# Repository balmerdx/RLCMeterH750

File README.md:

# RLCMeterH750
Это RLC построенный на STM32H750.
Основные отличительные особенности:
* использование быстрого 16-ти битного ADC от STM32H750
* широкий диапазон тестовых частот 10 Гц - 500 КГц
* построение графиков параметров в зависимости от частоты

Про точность не буду сильно распинаться, ибо сам точно не знаю.
Но приблизительно опишу.
Сопротивления измеряются в диапазоне от единиц миллиом до сотен килоом.
Но десятые доли пикофарада без проблемм можно измерить. На частотах 100 КГц и выше.
Десятки наногенри тоже вполне можно измерять. Тоже на высоких частотах, но тут желательно теорию подучить, чтобы понимать что измеряется.
На низких частотах вполне можно измерять десятки милифарад и единицы генри.

И да, внимание!!!! Финальной PCB нет в этом проекте. На плату RLCMeterH750_v2 я вкорячил детали от схемы RLCMeterH750_v3. Собственно говоря вариант RLCMeterH750_v2 тоже полностью рабочий, но он имеет отвратительно большие ошибки на частотах ниже 300 Гц. RLCMeterH750_v3 исправляет резонансы, которые были не учтены мной.

А ещё этот RLC измеритель умеет строить графики значений в зависимости от частоты. Вот пример измерения катушки индуктивности от реле. Красная линия - вещественная часть сопротивления, зелёная - мнимая часть сопротивления. Естественно железный сердечник ведёт себя совсем не так, как хорошая катушка индуктивности.

### Тут много ссылок на посты в Livejournal про то как шла разработка.
* [Пост 157420](https://balmerdx.livejournal.com/157420.html)
* [Пост 157827](https://balmerdx.livejournal.com/157827.html)
* [Пост 158370](https://balmerdx.livejournal.com/158370.html)
* [Пост 159728](https://balmerdx.livejournal.com/159728.html)
* [Пост 160005](https://balmerdx.livejournal.com/160005.html)
* [Пост 160708](https://balmerdx.livejournal.com/160708.html)
* [Пост 160803](https://balmerdx.livejournal.com/160803.html)
* [Пост 161141](https://balmerdx.livejournal.com/161141.html)
* [Пост 161592](https://balmerdx.livejournal.com/161592.html)

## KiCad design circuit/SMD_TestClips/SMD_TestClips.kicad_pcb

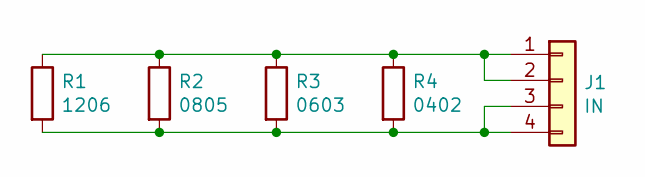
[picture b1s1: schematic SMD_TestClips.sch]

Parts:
J1: IN; PinHeader_1x04_P2.54mm_Vertical
R1: 1206; R_1206_3216Metric
R2: 0805; R_0805_2012Metric
R3: 0603; R_0603_1608Metric
R4: 0402; R_0402_1005Metric

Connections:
unnamed: J1.1, J1.2, R1.1, R2.1, R3.1, R4.1
unnamed: J1.3, J1.4, R1.2, R2.2, R3.2, R4.2

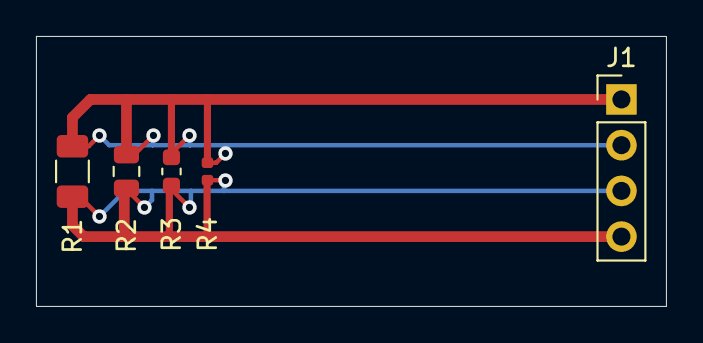
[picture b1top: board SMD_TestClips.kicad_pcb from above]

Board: 2 copper layers, 35.0 x 15.0 mm, 5 parts (0 on the bottom side), 2 nets.

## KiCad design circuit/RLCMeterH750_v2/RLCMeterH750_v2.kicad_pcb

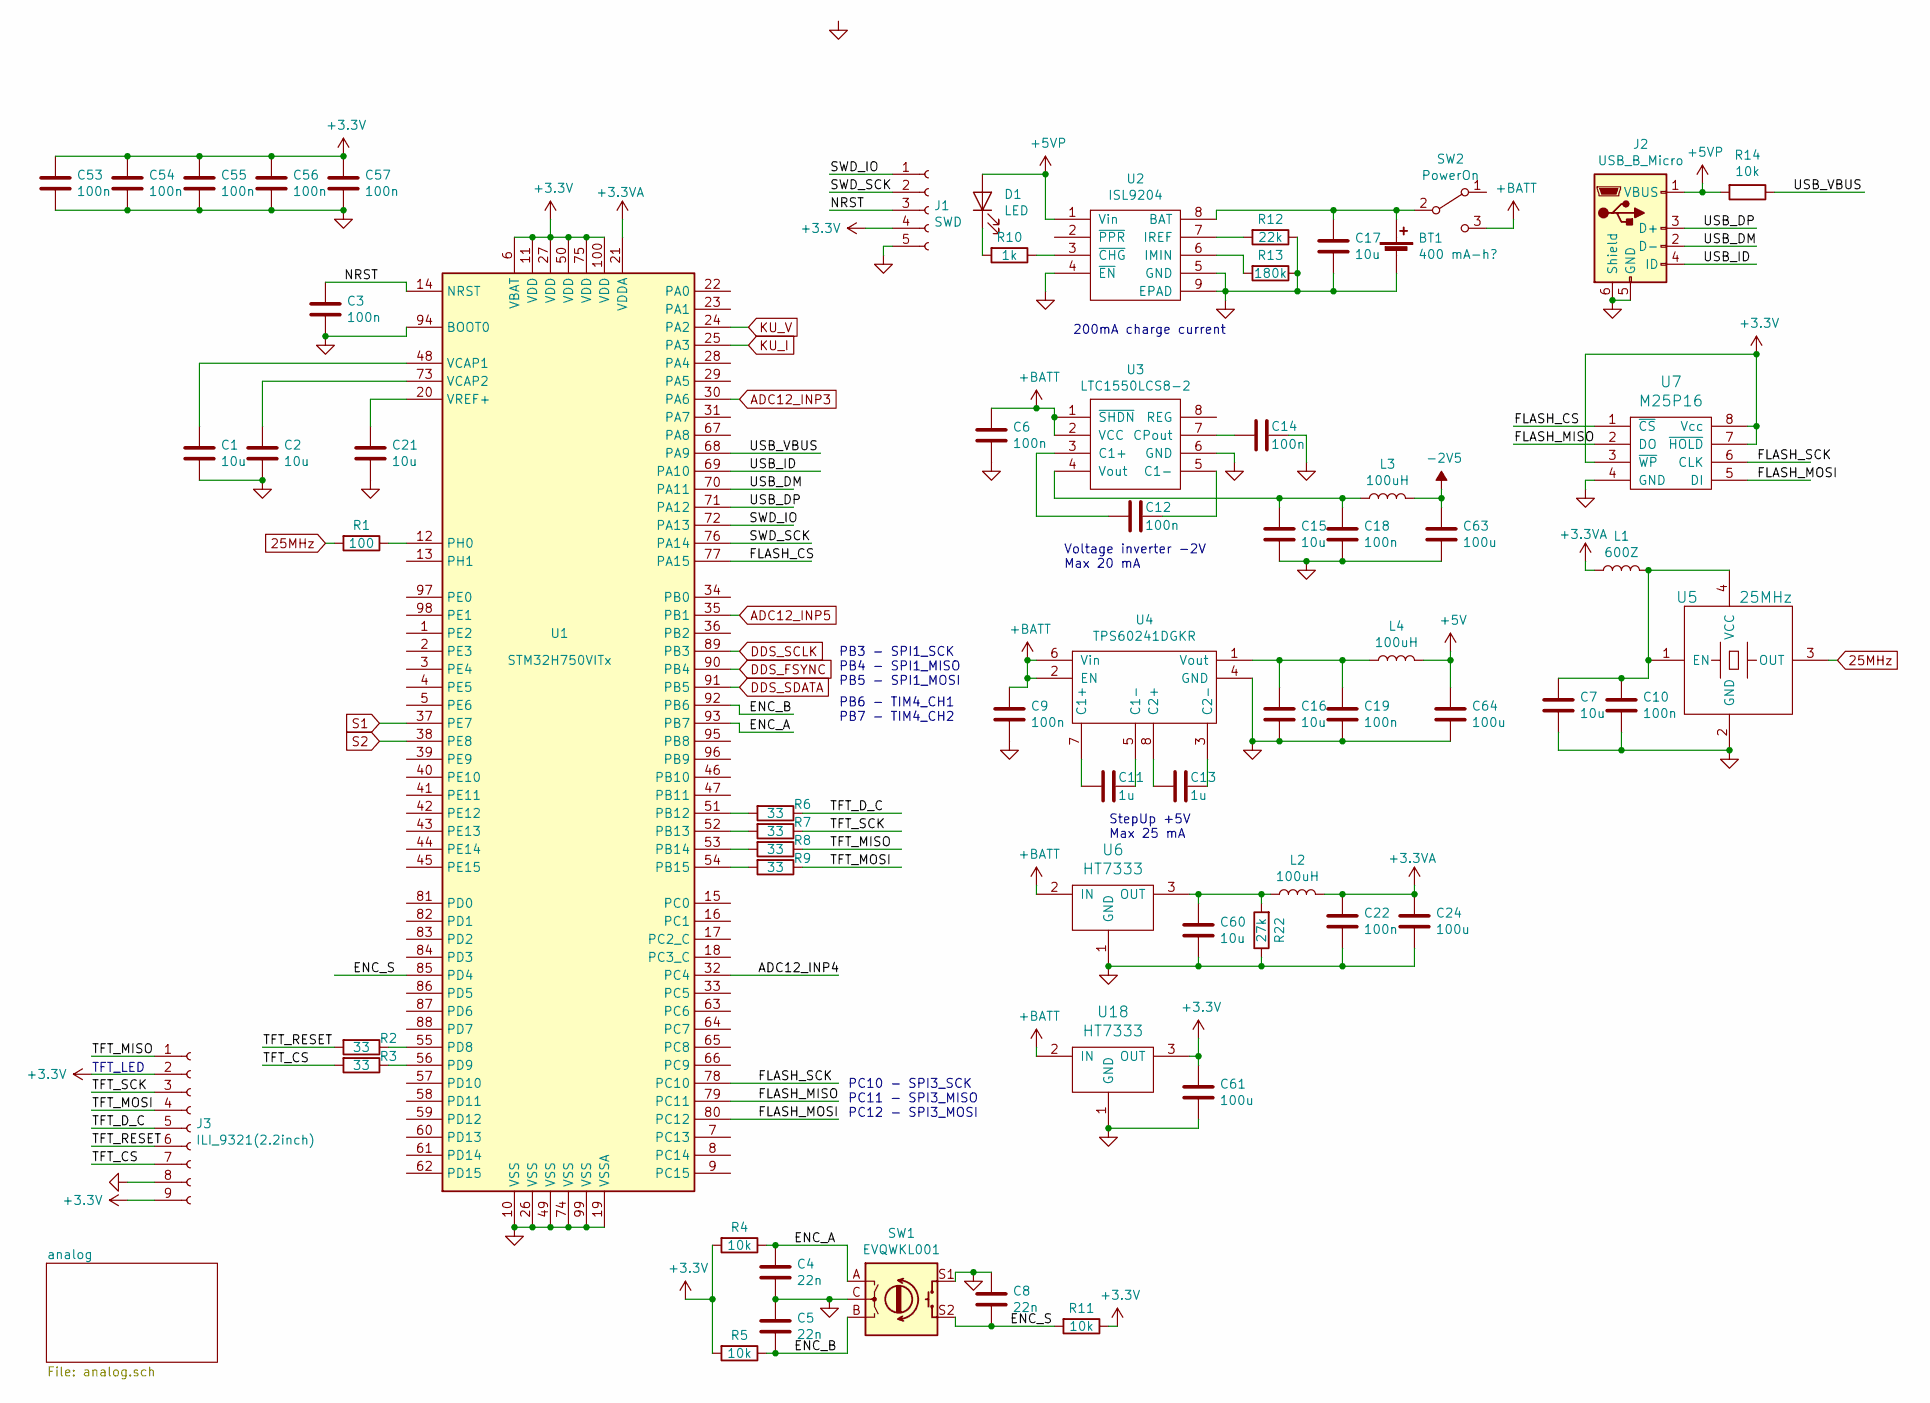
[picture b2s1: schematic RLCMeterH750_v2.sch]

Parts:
BT1: 400 mA-h?; PinSocket_1x02_P2.54mm_Vertical
C1, C2, C7, C15, C16, C17, C21, C60: 10u; C_1206_3216Metric
C3, C6, C9, C10, C12, C14, C18, C19, C22, C53, C54, C55, C56, C57: 100n; C_0603_1608Metric
C4, C5, C8: 22n; C_0603_1608Metric
C11, C13: 1u; C_0805_2012Metric
C24, C61, C63, C64: 100u; C_1206_3216Metric
D1: LED; LED_0805_2012Metric_Pad1.15x1.40mm_HandSolder
J1: SWD; PinSocket_1x05_P1.27mm_Vertical
J2: USB_B_Micro; USB_Micro-B_Molex-105017-0001
J3: ILI_9321(2.2inch)
L1: 600Z; L_1206_3216Metric
L2, L3, L4: 100uH; L_Axial_L5.3mm_D2.2mm_P7.62mm_Horizontal_Vishay_IM-1
R1: 100; R_0603_1608Metric
R2, R3, R6, R7, R8, R9: 33; R_0603_1608Metric
R4, R5, R11, R14: 10k; R_0603_1608Metric
R10: 1k; R_0603_1608Metric
R12: 22k; R_0603_1608Metric
R13: 180k; R_0603_1608Metric
R22: 27k; R_0603_1608Metric
SW1: EVQWKL001; Encoder_EVQWK4
SW2: PowerOn; SW_Angled_with_GND
U1: STM32H750VITx; LQFP-100_14x14mm_P0.5mm
U2: ISL9204; DFN-8-1EP_3x2mm_P0.5mm_EP1.75x1.65mm
U3: LTC1550LCS8-2; TSSOP-8_3x3mm_P0.65mm
U4: TPS60241DGKR; TSSOP-8_3x3mm_P0.65mm
U5: 25MHz; Crystal_5.0x3.2mm
U6, U18: HT7333; SOT-89-3
U7: M25P16; SOIC-8_3.9x4.9mm_P1.27mm

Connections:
25MHz: R1.2, U5.3 (OUT); also elsewhere on the board
+3.3VA: C22.1, C24.1, L1.1, L2.2, U1.21 (VDDA); also elsewhere on the board
+3V3: C53.1, C54.1, C55.1, C56.1, C57.1, C61.1, J1.4, J3.2, J3.9, R4.2, R5.2, R11.1, U1.6 (VBAT), U1.11 (VDD), U1.27 (VDD), U1.50 (VDD), U1.75 (VDD), U1.100 (VDD), U7.3 (~WP), U7.7 (~HOLD), U7.8 (Vcc), U18.3 (OUT)
+5V: C64.1, L4.2; also elsewhere on the board
+5VP: D1.2 (A), J2.1 (VBUS), R14.2, U2.1 (Vin)
+BATT: C6.1, C9.1, SW2.3 (C), U3.1 (~SHDN), U3.2 (VCC), U4.2 (EN), U4.6 (Vin), U6.2 (IN), U18.2 (IN)
-2V5: C63.1, L3.2; also elsewhere on the board
/ADC12_INP4: U1.32 (PC4)
/ENC_A: C4.1, R4.1, SW1.A, U1.93 (PB7)
/ENC_B: C5.2, R5.1, SW1.B, U1.92 (PB6)
/ENC_S: C8.2, R11.2, SW1.S2, U1.85 (PD4)
/FLASH_CS: U1.77 (PA15), U7.1 (~CS)
/FLASH_MISO: U1.79 (PC11), U7.2 (DO)
/FLASH_MOSI: U1.80 (PC12), U7.5 (DI)
/FLASH_SCK: U1.78 (PC10), U7.6 (CLK)
/NRST: C3.1, J1.3, U1.14 (NRST)
/SWD_IO: J1.1, U1.72 (PA13)
/SWD_SCK: J1.2, U1.76 (PA14)
/TFT_CS: J3.7, R3.2
/TFT_D_C: J3.5, R6.1
/TFT_MISO: J3.1, R8.1
/TFT_MOSI: J3.4, R9.1
/TFT_RESET: J3.6, R2.2
/TFT_SCK: J3.3, R7.1
/USB_DM: J2.2 (D-), U1.70 (PA11)
/USB_DP: J2.3 (D+), U1.71 (PA12)
/USB_ID: J2.4 (ID), U1.69 (PA10)
/USB_VBUS: R14.1, U1.68 (PA9)
ADC12_INP3: U1.30 (PA6); also elsewhere on the board
ADC12_INP5: U1.35 (PB1); also elsewhere on the board
DDS_FSYNC: U1.90 (PB4); also elsewhere on the board
DDS_SCLK: U1.89 (PB3); also elsewhere on the board
DDS_SDATA: U1.91 (PB5); also elsewhere on the board
GND: BT1.2 (-), C1.2, C2.2, C3.2, C4.2, C5.1, C6.2, C7.2, C8.1, C9.2, C10.2, C14.1, C15.2, C16.2, C17.2, C18.2, C19.2, C21.2, C22.2, C24.2, C53.2, C54.2, C55.2, C56.2, C57.2, C60.2, C61.2, C63.2, C64.2, J1.5, J2.5 (GND), J2.6 (Shield), J3.8, R12.1, R13.1, R22.1, SW1.C, SW1.GND, SW1.PAD, SW1.S1, U1.10 (VSS), U1.19 (VSSA), U1.26 (VSS), U1.49 (VSS), U1.74 (VSS), U1.94 (BOOT0), U1.99 (VSS), U2.4 (~EN), U2.5 (GND), U2.9 (EPAD), U3.6 (GND), U4.4 (GND), U5.2 (GND), U6.1 (GND), U7.4 (GND), U18.1 (GND); also elsewhere on the board
KU_I: U1.25 (PA3); also elsewhere on the board
KU_V: U1.24 (PA2); also elsewhere on the board
unnamed: BT1.1 (+), C17.1, SW2.2 (B), U2.8 (BAT)
unnamed: C1.1, U1.48 (VCAP1)
unnamed: C2.1, U1.73 (VCAP2)
unnamed: C7.1, C10.1, L1.2, U5.1 (EN), U5.4 (VCC)
unnamed: C11.1, U4.5 (C1-)
unnamed: C11.2, U4.7 (C1+)
unnamed: C12.1, U3.5 (C1-)
unnamed: C12.2, U3.3 (C1+)
unnamed: C13.1, U4.3 (C2-)
unnamed: C13.2, U4.8 (C2+)
unnamed: C14.2, U3.7 (CPout)
unnamed: C15.1, C18.1, L3.1, U3.4 (Vout)
unnamed: C16.1, C19.1, L4.1, U4.1 (Vout)
unnamed: C21.1, U1.20 (VREF+)
unnamed: C60.1, L2.1, R22.2, U6.3 (OUT)
unnamed: D1.1 (K), R10.2
unnamed: R1.1, U1.12 (PH0)
unnamed: R2.1, U1.55 (PD8)
unnamed: R3.1, U1.56 (PD9)
unnamed: R6.2, U1.51 (PB12)
unnamed: R7.2, U1.52 (PB13)
unnamed: R8.2, U1.53 (PB14)
unnamed: R9.2, U1.54 (PB15)
unnamed: R10.1, U2.3 (~CHG)
unnamed: R12.2, U2.7 (IREF)
unnamed: R13.2, U2.6 (IMIN)
S1: U1.37 (PE7); also elsewhere on the board
S2: U1.38 (PE8); also elsewhere on the board

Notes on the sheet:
200mA charge current
TFT_LED
Voltage inverter -2V Max 20 mA
StepUp +5V Max 25 mA
PB3 - SPI1_SCK PB4 - SPI1_MISO PB5 - SPI1_MOSI
PC10 - SPI3_SCK PC11 - SPI3_MISO PC12 - SPI3_MOSI
PB6 - TIM4_CH1 PB7 - TIM4_CH2

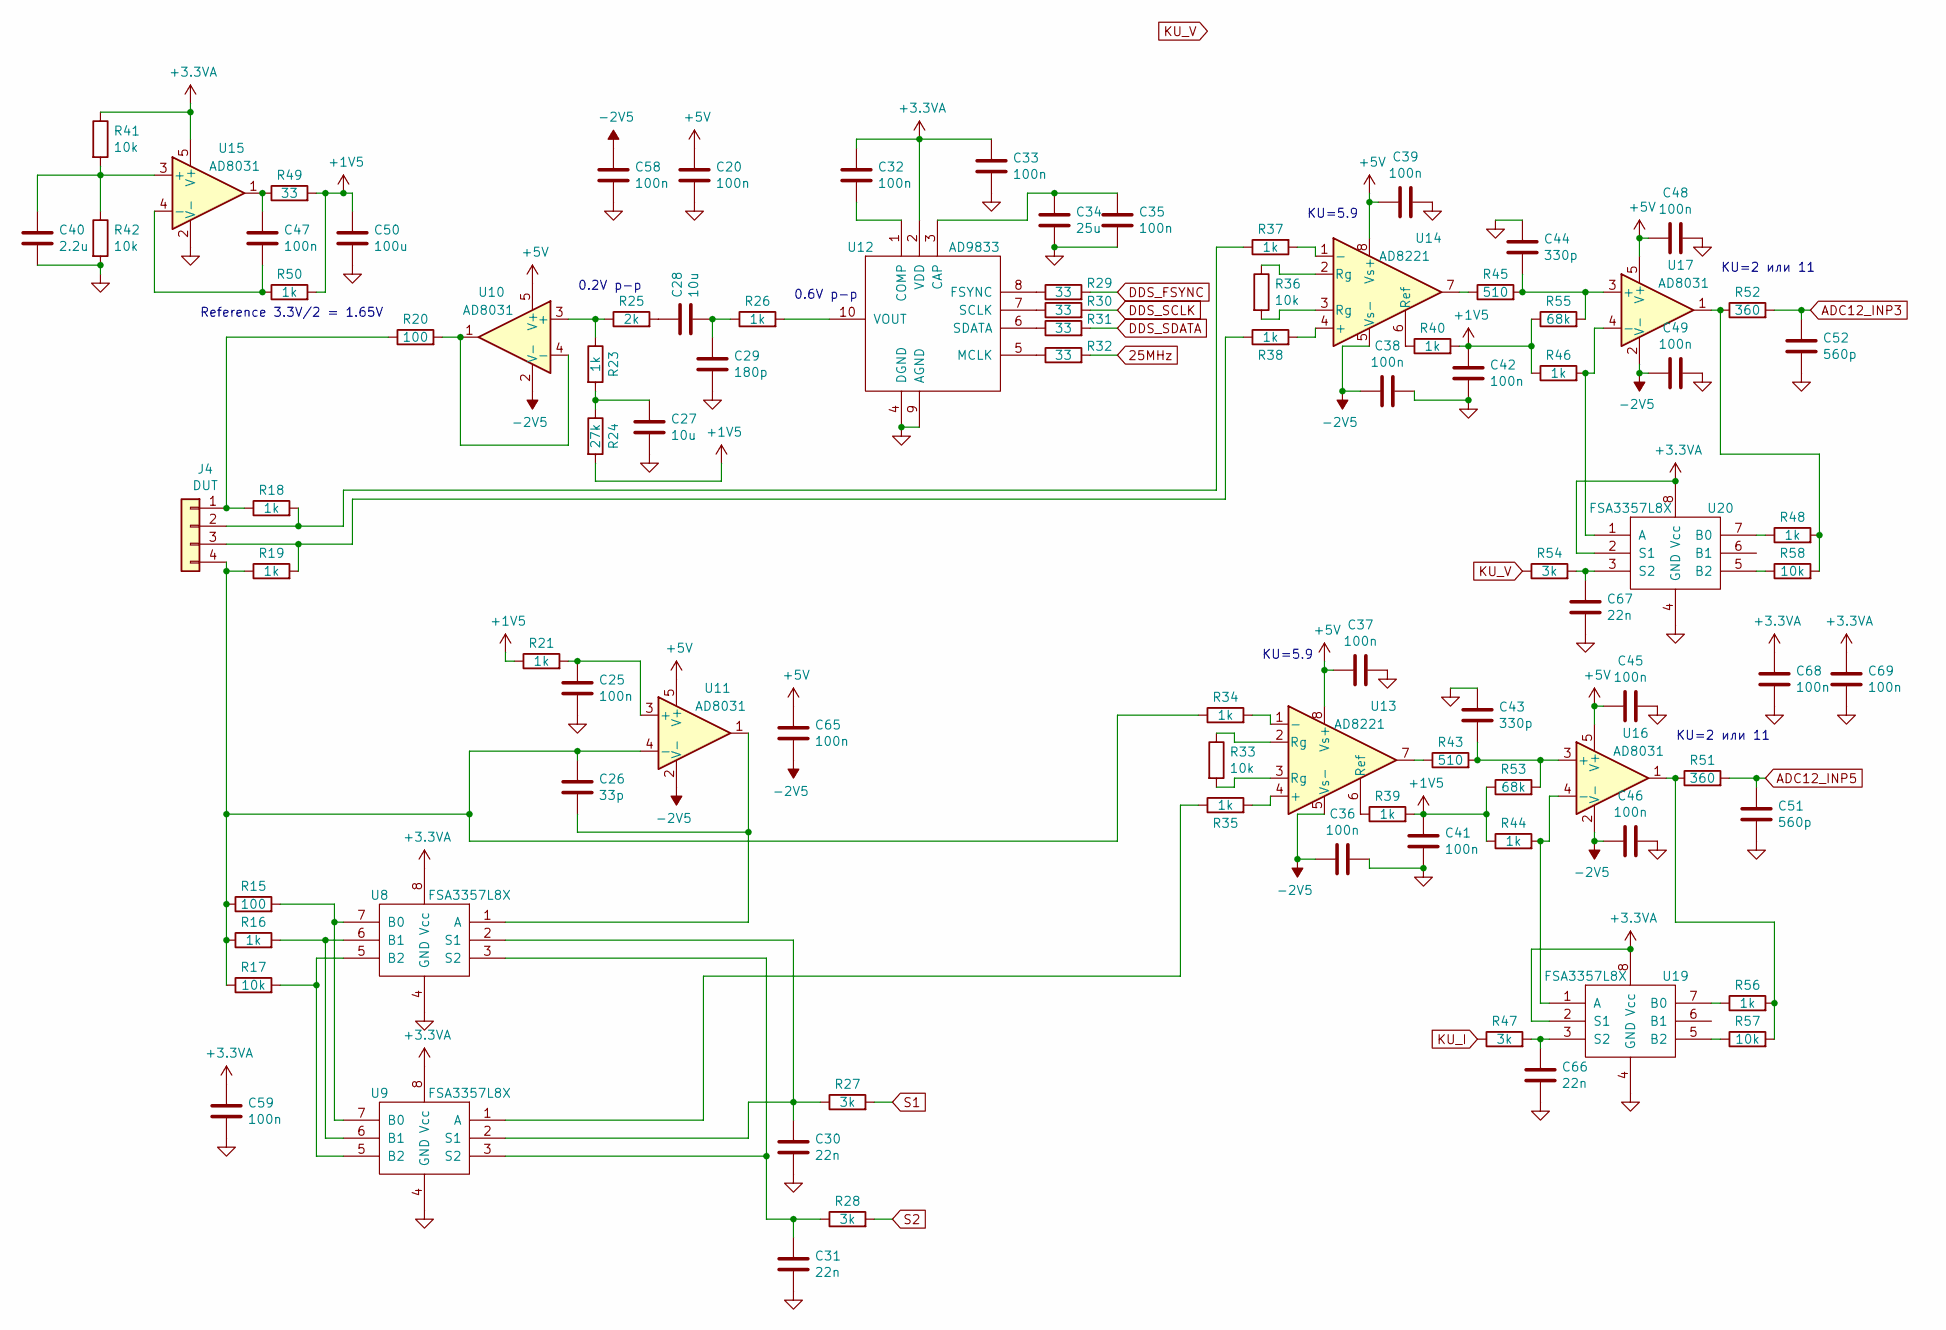
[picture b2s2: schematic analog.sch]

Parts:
C20, C25, C32, C33, C35, C36, C37, C38, C39, C41, C42, C45, C46, C47, C48, C49, C58, C59, C65, C68, C69: 100n; C_0603_1608Metric
C26: 33p; C_0603_1608Metric
C27, C28: 10u; C_1206_3216Metric
C29: 180p; C_0603_1608Metric
C30, C31, C66, C67: 22n; C_0603_1608Metric
C34: 25u; C_1206_3216Metric
C40: 2.2u; C_0805_2012Metric
C43, C44: 330p; C_1206_3216Metric
C50: 100u; C_1206_3216Metric
C51, C52: 560p; C_1206_3216Metric
J4: DUT; PinHeader_1x04_P2.54mm_Vertical
R15, R20: 100; R_0603_1608Metric
R16, R18, R19, R21, R23, R26, R34, R35, R37, R38, R39, R40, R44, R46, R48, R50, R56: 1k; R_0603_1608Metric
R17, R33, R36, R41, R42, R57, R58: 10k; R_0603_1608Metric
R24: 27k; R_0603_1608Metric
R25: 2k; R_0603_1608Metric
R27, R28, R47, R54: 3k; R_0603_1608Metric
R29, R30, R31, R32, R49: 33; R_0603_1608Metric
R43, R45: 510; R_0603_1608Metric
R51, R52: 360; R_0603_1608Metric
R53, R55: 68k; R_0603_1608Metric
U8, U9, U19, U20: FSA3357L8X; MicroPak_8-Lead
U10, U11, U15, U16, U17: AD8031; SOT-23-5
U12: AD9833; MSOP-10_3x3mm_P0.5mm
U13, U14: AD8221; MSOP-8_3x3mm_P0.65mm

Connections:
25MHz: R32.2; also elsewhere on the board
+1V5: C41.1, C42.1, C50.1, R21.1, R24.2, R39.2, R40.2, R44.1, R46.1, R49.2, R50.2, R53.1, R55.1
+3.3VA: C32.1, C33.1, C59.1, C68.1, C69.1, R41.1, U8.8 (Vcc), U9.8 (Vcc), U12.2 (VDD), U15.5 (V+), U19.2 (S1), U19.8 (Vcc), U20.2 (S1), U20.8 (Vcc); also elsewhere on the board
+5V: C20.1, C37.2, C39.2, C45.2, C48.2, C65.1, U10.5 (V+), U11.5 (V+), U13.8 (Vs+), U14.8 (Vs+), U16.5 (V+), U17.5 (V+); also elsewhere on the board
-2V5: C36.2, C38.2, C46.2, C49.2, C58.1, C65.2, U10.2 (V-), U11.2 (V-), U13.5 (Vs-), U14.5 (Vs-), U16.2 (V-), U17.2 (V-); also elsewhere on the board
ADC12_INP3: C52.1, R52.2; also elsewhere on the board
ADC12_INP5: C51.1, R51.2; also elsewhere on the board
DDS_FSYNC: R29.2; also elsewhere on the board
DDS_SCLK: R30.2; also elsewhere on the board
DDS_SDATA: R31.2; also elsewhere on the board
GND: C20.2, C25.2, C27.2, C29.2, C30.2, C31.2, C33.2, C34.2, C35.2, C36.1, C37.1, C38.1, C39.1, C40.2, C41.2, C42.2, C43.1, C44.1, C45.1, C46.1, C48.1, C49.1, C50.2, C51.2, C52.2, C58.2, C59.2, C66.2, C67.2, C68.2, C69.2, R42.2, U8.4 (GND), U9.4 (GND), U12.4 (DGND), U12.9 (AGND), U15.2 (V-), U19.4 (GND), U20.4 (GND); also elsewhere on the board
KU_I: R47.1; also elsewhere on the board
KU_V: R54.1; also elsewhere on the board
unnamed: C25.1, R21.2, U11.3 (+)
unnamed: C26.1, J4.4, R15.1, R16.1, R17.1, R19.1, R34.1, U11.4 (-)
unnamed: C26.2, U8.1 (A), U11.1
unnamed: C27.1, R23.2, R24.1
unnamed: C28.1, R25.2
unnamed: C28.2, C29.1, R26.1
unnamed: C30.1, R27.1, U8.2 (S1), U9.2 (S1)
unnamed: C31.1, R28.1, U8.3 (S2), U9.3 (S2)
unnamed: C32.2, U12.1 (COMP)
unnamed: C34.1, C35.1, U12.3 (CAP)
unnamed: C40.1, R41.2, R42.1, U15.3 (+)
unnamed: C43.2, R43.2, R53.2, U16.3 (+)
unnamed: C44.2, R45.2, R55.2, U17.3 (+)
unnamed: C47.1, R49.1, U15.1
unnamed: C47.2, R50.1, U15.4 (-)
unnamed: C66.1, R47.2, U19.3 (S2)
unnamed: C67.1, R54.2, U20.3 (S2)
unnamed: J4.1, R18.1, R20.1
unnamed: J4.2, R18.2, R37.1
unnamed: J4.3, R19.2, R38.1
unnamed: R15.2, U8.7 (B0), U9.7 (B0)
unnamed: R16.2, U8.6 (B1), U9.6 (B1)
unnamed: R17.2, U8.5 (B2), U9.5 (B2)
unnamed: R20.2, U10.1, U10.4 (-)
unnamed: R23.1, R25.1, U10.3 (+)
unnamed: R26.2, U12.10 (VOUT)
unnamed: R29.1, U12.8 (FSYNC)
unnamed: R30.1, U12.7 (SCLK)
unnamed: R31.1, U12.6 (SDATA)
unnamed: R32.1, U12.5 (MCLK)
unnamed: R33.1, U13.2 (Rg)
unnamed: R33.2, U13.3 (Rg)
unnamed: R34.2, U13.1 (-)
unnamed: R35.1, U9.1 (A)
unnamed: R35.2, U13.4 (+)
unnamed: R36.1, U14.2 (Rg)
unnamed: R36.2, U14.3 (Rg)
unnamed: R37.2, U14.1 (-)
unnamed: R38.2, U14.4 (+)
unnamed: R39.1, U13.6 (Ref)
unnamed: R40.1, U14.6 (Ref)
unnamed: R43.1, U13.7
unnamed: R44.2, U16.4 (-), U19.1 (A)
unnamed: R45.1, U14.7
unnamed: R46.2, U17.4 (-), U20.1 (A)
unnamed: R48.1, U20.7 (B0)
unnamed: R48.2, R52.1, R58.2, U17.1
unnamed: R51.1, R56.2, R57.2, U16.1
unnamed: R56.1, U19.7 (B0)
unnamed: R57.1, U19.5 (B2)
unnamed: R58.1, U20.5 (B2)
S1: R27.2; also elsewhere on the board
S2: R28.2; also elsewhere on the board

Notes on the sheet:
Reference 3.3V/2 = 1.65V
KU=2 или 11
KU=5.9
0.6V p-p
0.2V p-p

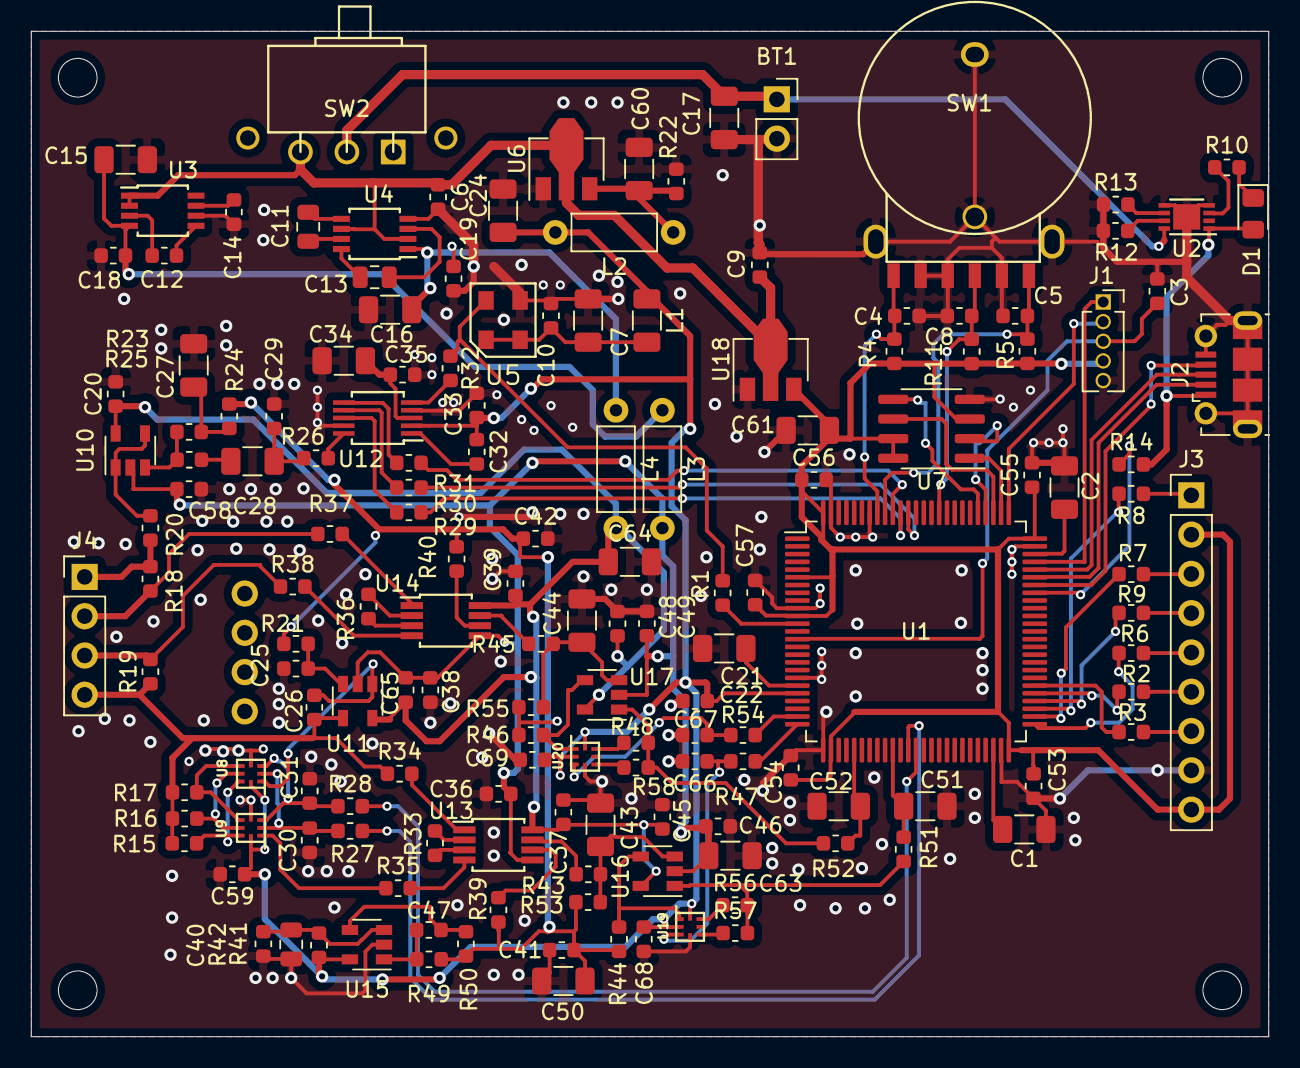
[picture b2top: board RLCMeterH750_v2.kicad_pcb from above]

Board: 2 copper layers, 80.0 x 65.0 mm, 157 parts (0 on the bottom side), 115 nets.

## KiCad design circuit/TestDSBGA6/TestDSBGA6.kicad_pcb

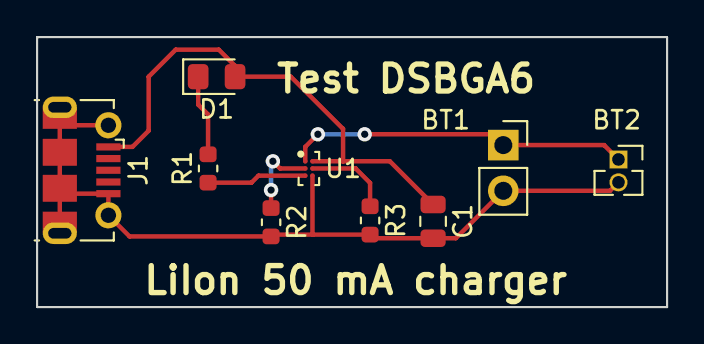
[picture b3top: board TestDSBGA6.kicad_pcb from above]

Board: 2 copper layers, 35.0 x 15.0 mm, 9 parts (0 on the bottom side), 7 nets.

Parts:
BT1: 2.54mm; PinSocket_1x02_P2.54mm_Vertical
BT2: 1.25mm; PinSocket_1x02_P1.27mm_Vertical
C1: 1u; C_0805_2012Metric
D1: LED; LED_0805_2012Metric_Pad1.15x1.40mm_HandSolder
J1: USB_B_Micro; USB_Micro-B_Molex-105017-0001
R1: 1k; R_0603_1608Metric
R2: 10k; R_0603_1608Metric
R3: 3.3k; R_0603_1608Metric
U1: BQ25101; DSBGA-6_0.4mm

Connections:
GND: BT1.2, BT2.2, C1.2, J1.5, J1.6, R2.2, R3.2, U1.C2
unnamed: BT1.1, BT2.1, U1.A1
unnamed: C1.1, D1.2, J1.1, U1.A2
unnamed: D1.1, R1.2
unnamed: R1.1, U1.C1
unnamed: R2.1, U1.B1
unnamed: R3.1, U1.B2

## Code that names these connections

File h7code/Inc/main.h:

#pragma once

//PCB_V3 макрос для третьей версии платы.
//Основных отличия два:
// - VREF+ от STM32H7 подключен только к конденсатору, поэтому требуется включить внутренний LDO на 2.5 вольт
// - переключаемый коэффициэнт усиления PA2 - KU_V, PA3 - KU_I

#include <stdbool.h>
#include <complex.h>
#include <string.h>


#ifdef __cplusplus
extern "C" {
#endif

#include "stm32h7xx_hal.h"
#include "interface/interface.h"
#include "interface/colors.h"
#include "interface/font_condensed30.h"
#include "interface/font_condensed59.h"
#include "settings.h"

// Exported functions prototypes ---------------------------------------------
void Error_Handler(void);

// Private defines -----------------------------------------------------------
#define STLK_RX_Pin GPIO_PIN_8
#define STLK_RX_GPIO_Port GPIOD
#define STLK_TX_Pin GPIO_PIN_9
#define STLK_TX_GPIO_Port GPIOD
#define USB_PowerSwitchOn_Pin GPIO_PIN_6
#define USB_PowerSwitchOn_GPIO_Port GPIOG
#define USB_OverCurrent_Pin GPIO_PIN_7
#define USB_OverCurrent_GPIO_Port GPIOG
#define USB_SOF_Pin GPIO_PIN_8
#define USB_SOF_GPIO_Port GPIOA
#define USB_VBUS_Pin GPIO_PIN_9
#define USB_VBUS_GPIO_Port GPIOA
#define USB_ID_Pin GPIO_PIN_10
#define USB_ID_GPIO_Port GPIOA
#define USB_DM_Pin GPIO_PIN_11
#define USB_DM_GPIO_Port GPIOA
#define USB_DP_Pin GPIO_PIN_12
#define USB_DP_GPIO_Port GPIOA

#ifdef __cplusplus
}
#endif

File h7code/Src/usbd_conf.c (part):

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    __HAL_RCC_GPIOA_CLK_ENABLE();
    /**USB_OTG_FS GPIO Configuration    
    PA8     ------> USB_OTG_FS_SOF
    PA9     ------> USB_OTG_FS_VBUS
    PA10     ------> USB_OTG_FS_ID
    PA11     ------> USB_OTG_FS_DM
    PA12     ------> USB_OTG_FS_DP 
    */
    GPIO_InitStruct.Pin = USB_SOF_Pin|USB_ID_Pin|USB_DM_Pin|USB_DP_Pin;
    GPIO_InitStruct.Mode = GPIO_MODE_AF_PP;
    GPIO_InitStruct.Pull = GPIO_NOPULL;
    GPIO_InitStruct.Speed = GPIO_SPEED_FREQ_LOW;
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  
    /**USB_OTG_FS GPIO Configuration    
    PA8     ------> USB_OTG_FS_SOF
    PA9     ------> USB_OTG_FS_VBUS
    PA10     ------> USB_OTG_FS_ID
    PA11     ------> USB_OTG_FS_DM
    PA12     ------> USB_OTG_FS_DP 
    */
    HAL_GPIO_DeInit(GPIOA, USB_SOF_Pin|USB_VBUS_Pin|USB_ID_Pin|USB_DM_Pin 
                          |USB_DP_Pin);

    /* Peripheral interrupt Deinit*/
    HAL_NVIC_DisableIRQ(OTG_FS_IRQn);
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
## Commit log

2019-09-28 initial gitignore
2019-09-29 schematic continue
2019-10-01 - crystal 25 MHz + AD9833
2019-10-06 - вродебы нарисовали аналоговую часть
2019-10-07 - add encoder
2019-10-12 - то, что успели нарисовать в свободное время
2019-10-12 - вроде все провода соединили
2019-10-13 - расставляли номера деталей, чтобы их было видно на плате
2019-10-13 - DRC ok
2019-10-16 - немного причесали внешний вид платы
2019-10-17 - версия, которую отошлем на завод
2019-11-02 - залили тестовый проект, правда без папки Drivers ибо она слишком большая
2019-11-02 - ненужный файл
2019-11-13 - запустили код на STM32H750
2019-11-16 - энкодер заработал
2019-11-16 - немпешно работающий дисплей
2019-11-16 - дисплей правильно развернут и более-менее быстро рисует
2019-11-16 - рабочий software SPI для AD9833
2019-11-16 - не получилось с hardware SPI, будем пользоваться software варимнтом
2019-11-17 - НЕ рабочий код ADC
2019-11-17 - переместили буфер ADC в D1 память и теперь до него может добраться DMA
2019-11-17 - remove eth code
2019-11-17 - конверсия данных успешно проходит
2019-11-23 - вынесли процессинг данных из прерывания
    - начали отсылать данные на клиентскую часть, чтобы глянуть их
2019-11-23 - успешно прочитали данные из устройства и увидели красивый синус
2019-11-23 - правильное clock source для ADC
2019-11-23 - корректное измерение частоты входного сигнала
2019-11-23 - замеряли скорость работы нашего sin_cos табличного
2019-11-23 - проверили, часто ли происходит adc buffer overrun
2019-11-24 - вычисления sin в пределах int32_t
    - первые результаты отсэмплированных данных
2019-11-25 - рассчитываем Z (пока без корректировки)
    - переключаем резистор на предпочтительный диапазон
2019-11-26 - misc
2019-12-01 - стали использовать тип complex (все равно мало вычислений, можно double использовать)
    - вывели FFT на python
    - стерли часть отладочного кода
2019-12-01 - еще немного убрались в коде
2019-12-01 - успешно проверили чтение Zx в зависимости от частоты по USB
2019-12-03 - немножко начали писать интерфейс
2019-12-04 - не до конца разведенная вторая версия платы
2019-12-05 - все дорожки развели
2019-12-05 - положение номеров деталей на плате
2019-12-06 - работающий delay
2019-12-07 - проверили erase/read/write flash правда только в начале
2019-12-07 - более узкий корпус для m25p16
2019-12-07 - версия для завода
2019-12-07 - вывели R re, im в single freq диалоге
2019-12-08 - проверили, что меню работает
2019-12-08 - непроверенный, но компилирующийся corrector
2019-12-09 - начали делать диалог калибровки
2019-12-10 - возможность вручную выбрать резистор для калибровки
2019-12-10 - для open calibration используем все резисторы
2019-12-11 - калибровка вполне честно работает
2019-12-12 - немного причесали вывод сопротивления в диалоге
2019-12-13 - вывели L/C
2019-12-15 - немного причесали single freq диалог
    - заодно чутка подправили неверный выбор резистора
2019-12-15 - ещё немного улучшили вид диалога
2019-12-18 - более-менее корректно показываем бесконечность
2019-12-20 - добавили в фонт ± и °, пришлось правда фонт уменьшить с 20 до 19.5 ибо что-то поменялось в системе.
2019-12-20 - view abs(Z) & arg(Z)
2019-12-22 - высчитали что-то похожее на ошибку
2019-12-22 - разместили на правильном месте ошибку, и она даже что-то разумное показывает
2019-12-23 - начали делать меню с графиком
2019-12-25 - сканируем интервал и показываем график cimag()
2019-12-25 - правильные значения по оси X на графике
2019-12-28 - рисуем графики
    - при получение данных по USB не забываем ставить паузу между установкой частоты и сэмплированием
2019-12-29 - исправили схему для большей точности на 400 Гц (криво правда, потом еще поправим)
    - plot теперь корректно очищает линию на краях интервала
    - scene_graph можно возюкать линией туда-сюда
2019-12-30 - отображение текущих параметров при отрисовке графика
2019-12-30 - коэффициенты калибровки теперь интерполируются
2020-01-01 - L/C теперь на графике интерпретируется для текущей частоты
    - HAL + CMSIS
2020-01-02 - непроверенное store_to_spi_flash.c
2020-01-03 - TestStoreToFlash --ok
2020-01-04 - начали запоминать текущие настройки
2020-01-04 - вынесли все, что связанно с correction в отдельное меню
    - появился выбор из трёх correction вариантов
2020-01-06 - начали делать корпус
2020-01-07 - вроде разместили на местах все элементы находчщиеся внутри коробочки
2020-01-07 - корпус с крышкой но без отверстий и направляющих под винты
2020-01-07 - дырки под дисплей
2020-01-08 - крепления под плату
    - переместили немного вверх плату, была явная ошибка в высоте дисплея
2020-01-08 - вырезы под плату
2020-01-08 - вырезы под выключатели и расширение над дисплеем
2020-01-08 - винты для крышки
2020-01-18 _v3.kicad - версия которая запаяна поверх платы _v2
2020-01-19 - gain_V gain_I надо было умножать, а не делить.
    Раньше не проявлялось, так как коэффициэнты были одинаковыми.
2020-01-19 - выбор gain i/v автоматический
2020-01-19 - калибровка 10 КОм и 10КОм+ работает корректно (впрочем как и все остальные диавазоны)
2020-01-20 - простейший диаложик для выбора Float
2020-01-20 - указание точного сопротивления перед калибровкой
2020-01-21 - не пишем слишком большие L и C
    - начали рисовать графики L и C
2020-01-22 - где-то в уголку писать pF или mH и т.д.
2020-01-24 - 0 ом резистор на выходе ОУ
    - не скалируется график фазы
    - стандартные частоты расположены по ряду E12 (экспоненциально)
    - добавили коэффииэнты к графикам (KOm, MOm и т.д.)
2020-02-04 - все наши страдания с нелинейностью ADC
    - debug menu
2020-02-05 - мало/много частот при вращении энкодера single freq
    - нижнюю панельку на Single Freq всю синим залили
2020-04-12 - firmware
2020-04-16 - начинаем писать readme
2020-04-16 - ссылка
2020-04-16 - простенький readme
2020-04-16 - readme
2020-04-16 - readme 4
2020-04-17 - readme написали про графики
2020-04-17 - синяя -> зелёная
2023-03-18 - AdcSamplesPerSecond 17 clock per asquision
    Оказывается, что количество тактов, которое требуется на сэмплирование
    одного ADC сэмпла определялось неверно. Но при этом каким-то чудом всё
    работало. Исправил это недоразумение.
2023-03-20 C47, C? 100n -> 100p, R33, R36 10k -> 15k
    C47, C? исправлен номинал на 100 pF
    R33, R36 исправлен номинал на 15 КОм
2023-05-01 - add make_sources

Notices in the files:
h7code/Src/usbd_conf.c:
© Copyright (c) 2019 STMicroelectronics.
All rights reserved.
This software component is licensed by ST under Ultimate Liberty license
(C) COPYRIGHT STMicroelectronics *****END OF FILE
